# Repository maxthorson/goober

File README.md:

# Goober

Goober is a compact USB-C macro pad project with two connected halves:

- `website/` contains the public Next.js site for presenting the product, linking
  firmware resources, and experimenting with a hosted QMK configurator surface.
- `hardware/` contains the Rev A hardware package: KiCad PCB files, case models,
  QMK firmware, fabrication docs, mockups, validation notes, and release
  deliverables.

The hardware target is a 9-key RP2040-Zero macro pad with MX hot-swap switches,
an OLED display, a volume/mute knob, and individually addressable RGB lighting.
USB hub and charging passthrough are deferred.

## Project Status

Rev A.1 is a checked engineering prototype ready for a first fabrication and fit
test. It has not yet been built or electrically tested on physical hardware.

The hardware package passes schematic ERC, PCB DRC, and KiCad schematic/PCB
parity checks with zero issues. Firmware compiles, and the printable case
components validate as watertight single-body meshes.

## Repository Layout

| Folder | Purpose |
|---|---|
| `website/` | Next.js product site and QMK configurator integration |
| `hardware/case/` | OpenSCAD source and printable STL case files |
| `hardware/docs/` | Design, fabrication, assembly, firmware, and validation guides |
| `hardware/firmware/` | QMK board files, keymap, build script, and UF2 output |
| `hardware/hardware/` | KiCad schematic, PCB, Gerbers, BOM, and part references |
| `hardware/mockups/` | CAD renders, board images, and appearance concepts |
| `hardware/releases/` | Packaged Rev A prototype release archive |
| `hardware/tools/` | Project-owned helper scripts; large external tools are excluded |

## Start Here

For the site:

```bash
cd website
npm install
npm run dev
```

For the hardware:

1. Read `hardware/docs/DESIGN_PLAN.md` and
   `hardware/docs/PARTS_AND_COST.md`.
2. Use `hardware/docs/FABRICATION.md` to order a small PCB batch.
3. Print the fit coupon, then follow `hardware/docs/ASSEMBLY_AND_TEST.md`.
4. Flash the supplied UF2 or rebuild from `hardware/firmware/`.

## Notes

Large installed tools, virtual environments, downloaded toolchains, and upstream
source checkouts are intentionally not committed. License and provenance notes
for the hardware package are in `hardware/NOTICE.md`.

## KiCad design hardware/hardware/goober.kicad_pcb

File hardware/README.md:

# goober

A compact 9-key USB-C macro pad with MX hot-swap switches, an OLED, a volume/mute knob and individually addressable RGB lighting. RP2040-Zero + QMK. **USB hub and charging passthrough are deferred.**

**Rev A.1 is a checked engineering prototype, ready for a first fabrication and fit test. It has not yet been built or electrically tested on hardware.**

## Start here

1. Read [the design plan](docs/DESIGN_PLAN.md) and [parts/cost list](docs/PARTS_AND_COST.md).
2. Use [the fabrication guide](docs/FABRICATION.md) to order a small PCB batch.
3. Print the fit coupon, then follow [assembly and testing](docs/ASSEMBLY_AND_TEST.md).
4. Flash the supplied UF2. [Software and firmware instructions](docs/SOFTWARE_AND_FIRMWARE.md) explain editing and rebuilding.

KiCad, OpenSCAD and the firmware build tools are already installed on this Mac. You only need an optional printer slicer if printing at home. Your remaining work is choosing switches/keycaps, buying parts, printing or ordering the enclosure, soldering and testing the physical prototype.

## Files

| Deliverable | Location |
|---|---|
| Bare-board manufacturing ZIP | [Goober-Rev-A-Gerbers.zip](hardware/Goober-Rev-A-Gerbers.zip) |
| Editable PCB/schematic | [KiCad project](hardware/goober.kicad_pro) — keep adjacent files/libraries together |
| Printable case | [Base](case/goober-base.stl), [lid](case/goober-lid.stl), [knob](case/goober-knob.stl), [fit coupon](case/goober-fit-coupon.stl) |
| Editable case | [OpenSCAD source](case/goober.scad) |
| Ready-to-flash firmware | [Goober UF2](firmware/build/goober-rev-a-default.uf2) |
| Firmware source | [Default keymap](firmware/goober/rev_a/keymaps/default/keymap.c), plus board files in `firmware/goober/rev_a/` |
| Mockups | [Actual CAD](mockups/goober-cad.png), [exploded CAD](mockups/goober-exploded.png), [appearance concept](mockups/goober-appearance.png) |
| Parts list | [Guide](docs/PARTS_AND_COST.md), [CSV](hardware/BOM.csv) |
| Checks and remaining tests | [Validation record](docs/VALIDATION.md) |

The design passes schematic ERC, PCB DRC and KiCad schematic/PCB parity with zero issues. Firmware compiles; the base, lid and knob are watertight single-body meshes. The release includes the detailed validation results and checksums.

The archive in `releases/` contains the deliverables and editable project, without the large installed tools and upstream source checkouts. License/provenance notes are in [NOTICE.md](NOTICE.md).

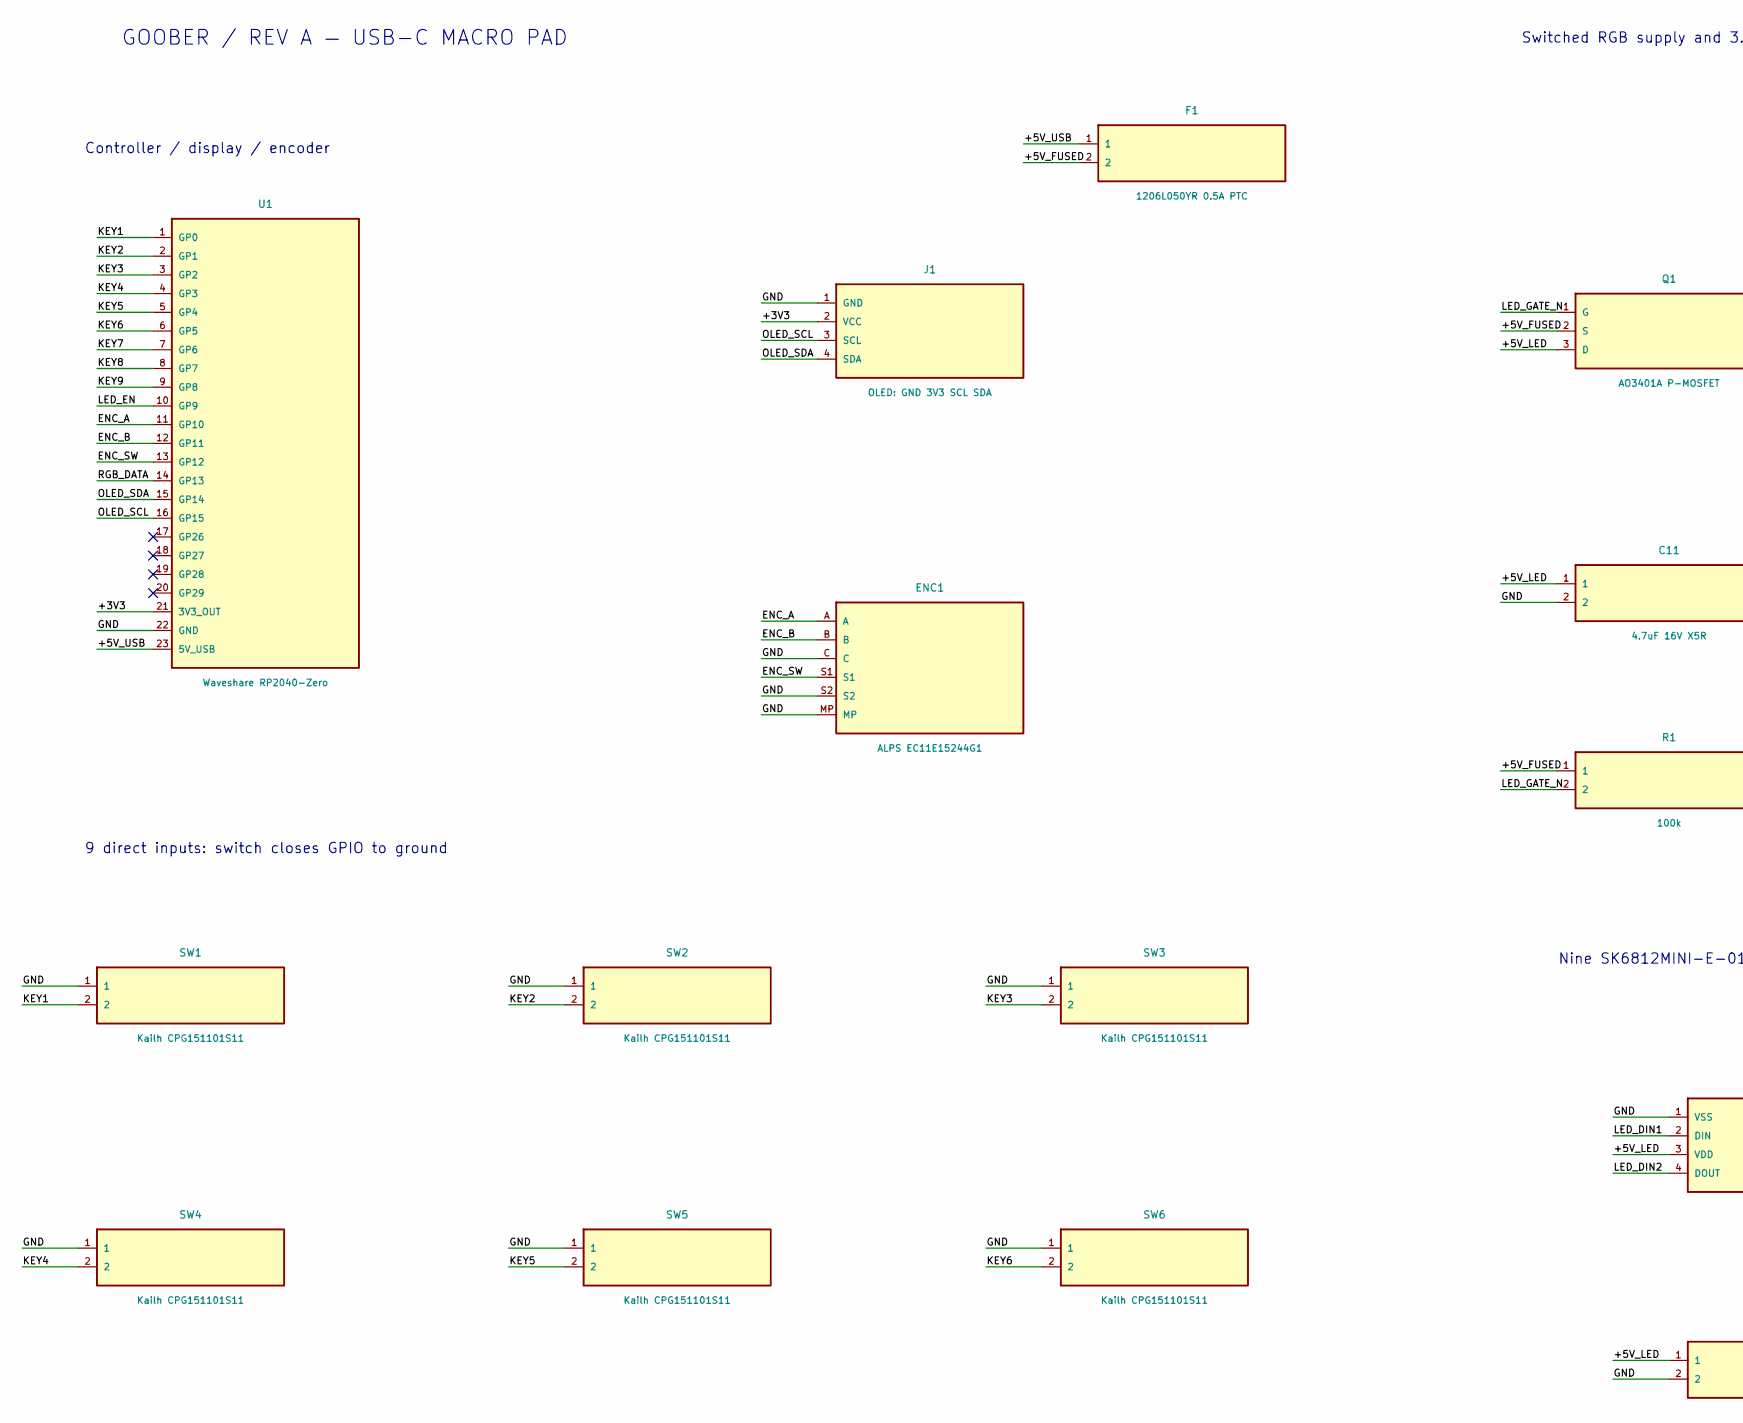
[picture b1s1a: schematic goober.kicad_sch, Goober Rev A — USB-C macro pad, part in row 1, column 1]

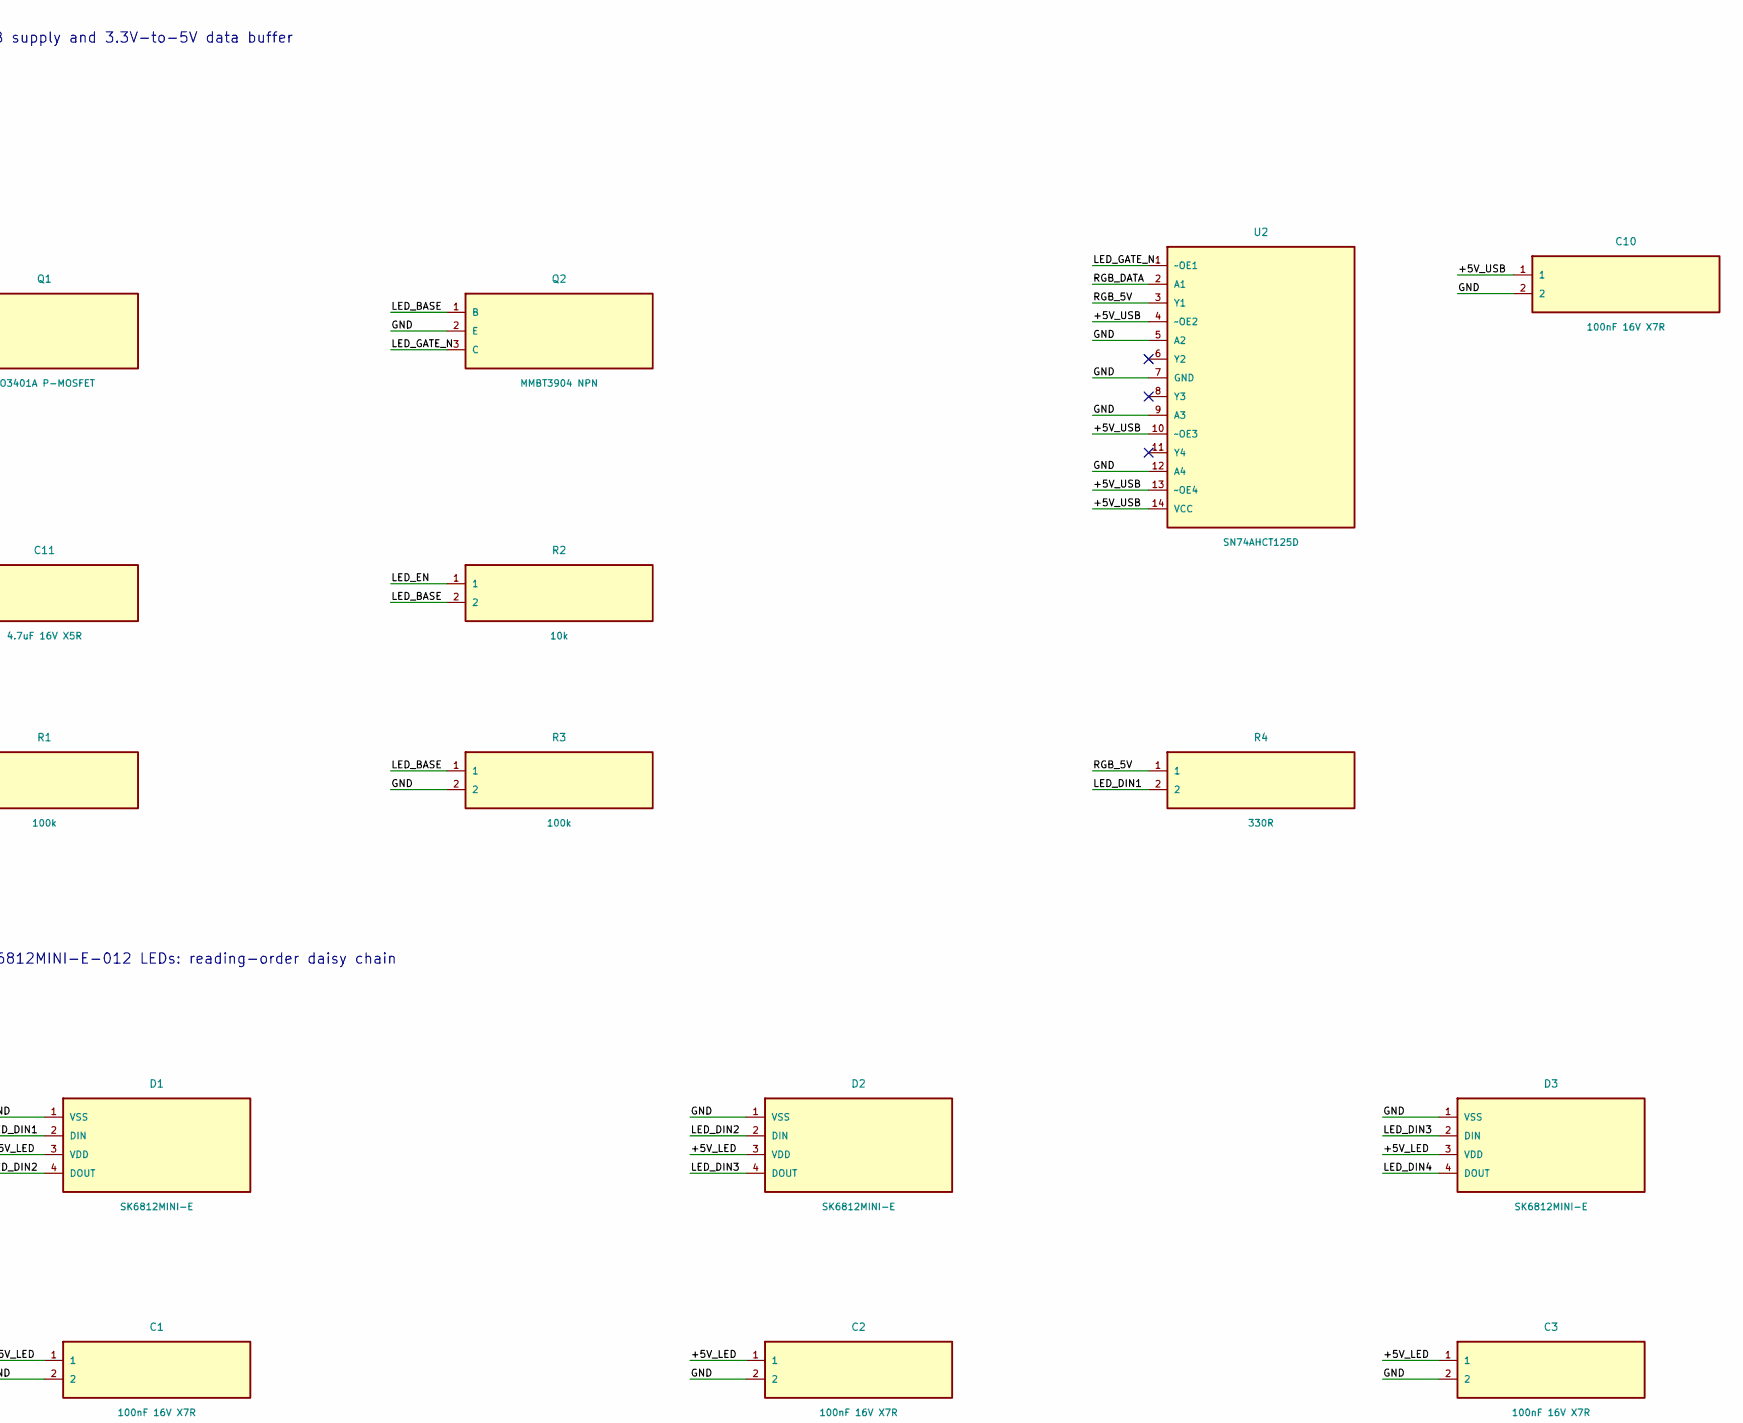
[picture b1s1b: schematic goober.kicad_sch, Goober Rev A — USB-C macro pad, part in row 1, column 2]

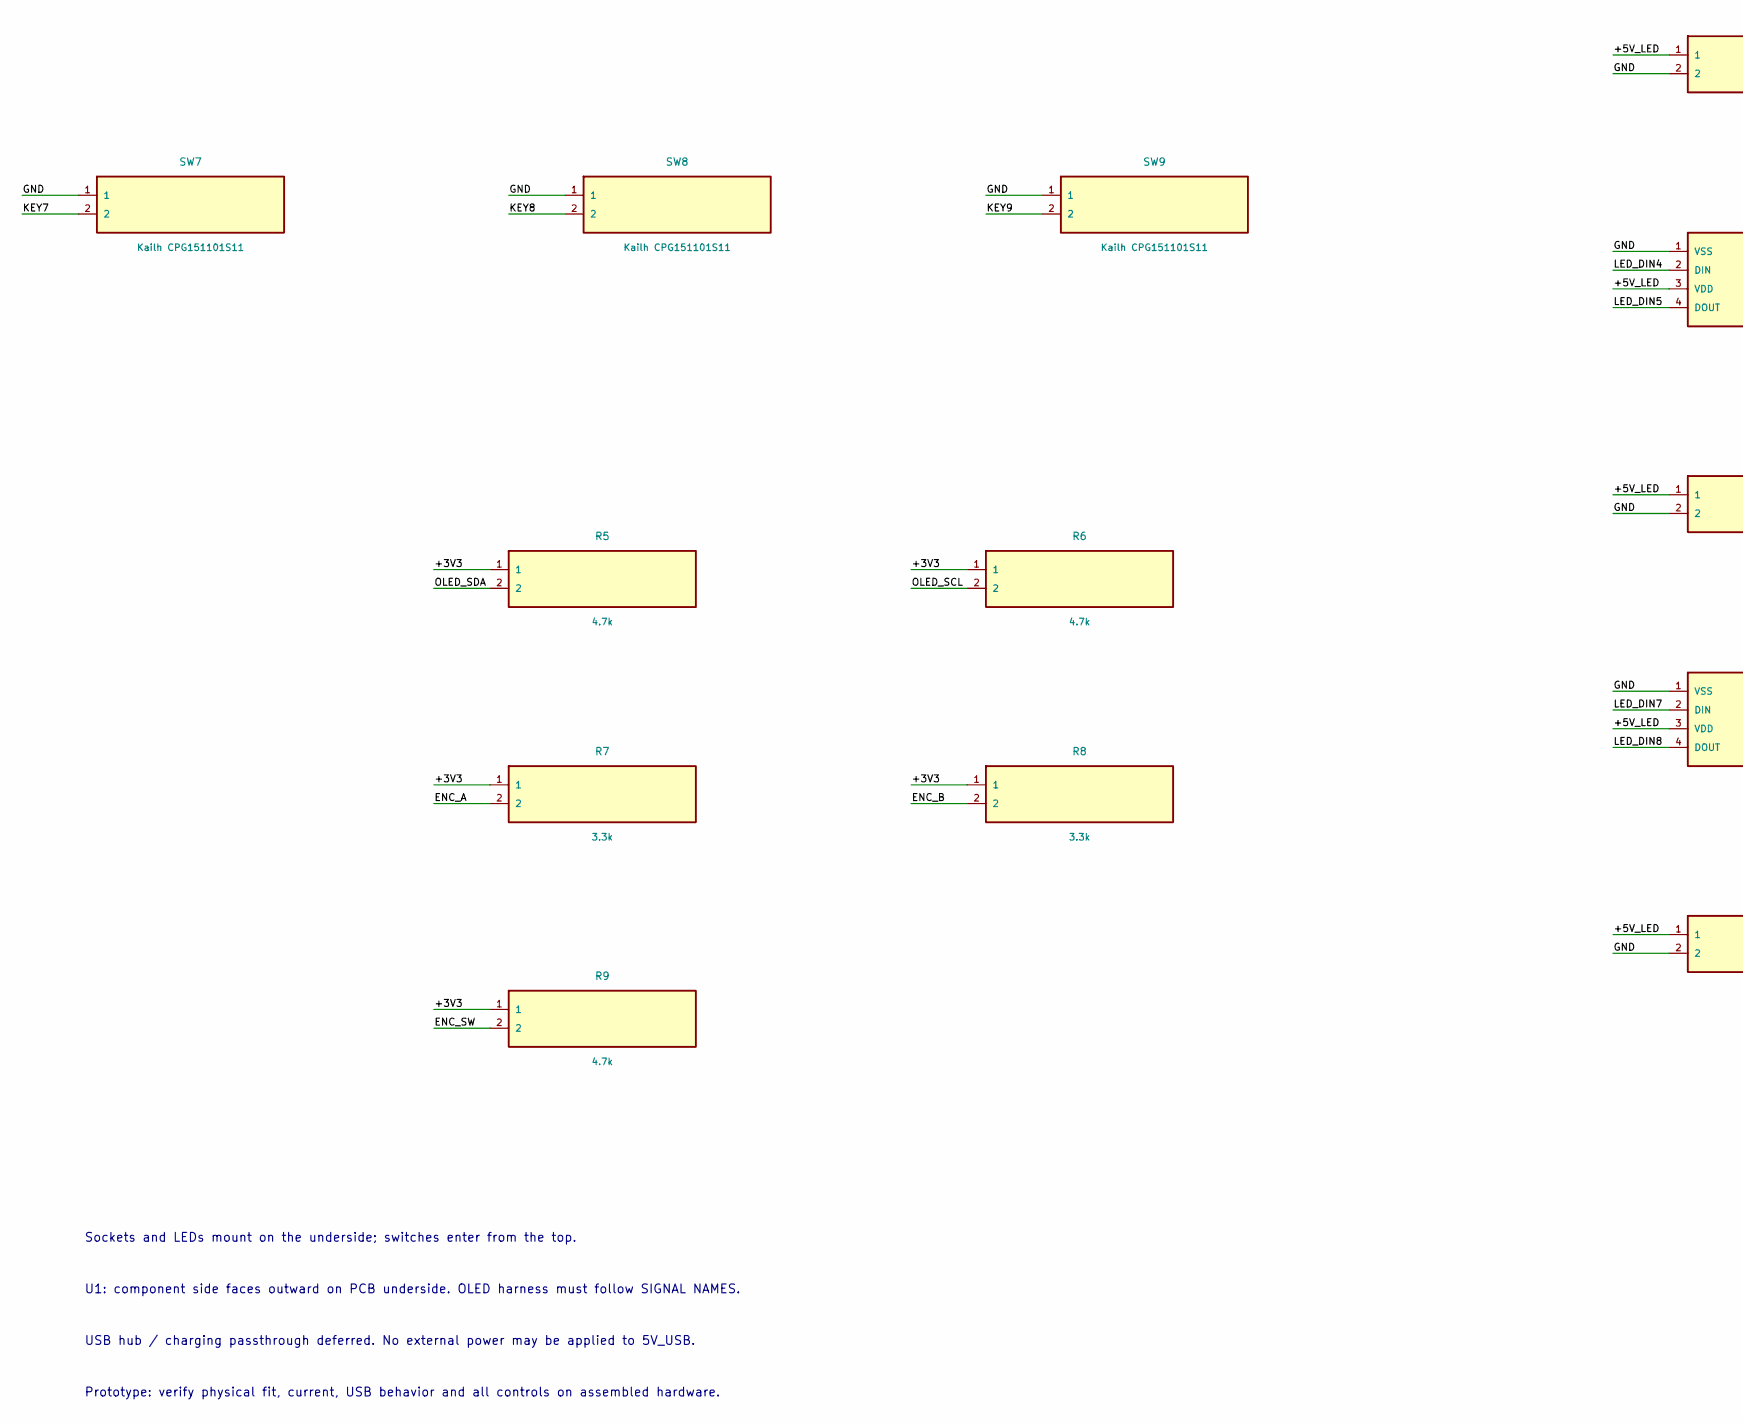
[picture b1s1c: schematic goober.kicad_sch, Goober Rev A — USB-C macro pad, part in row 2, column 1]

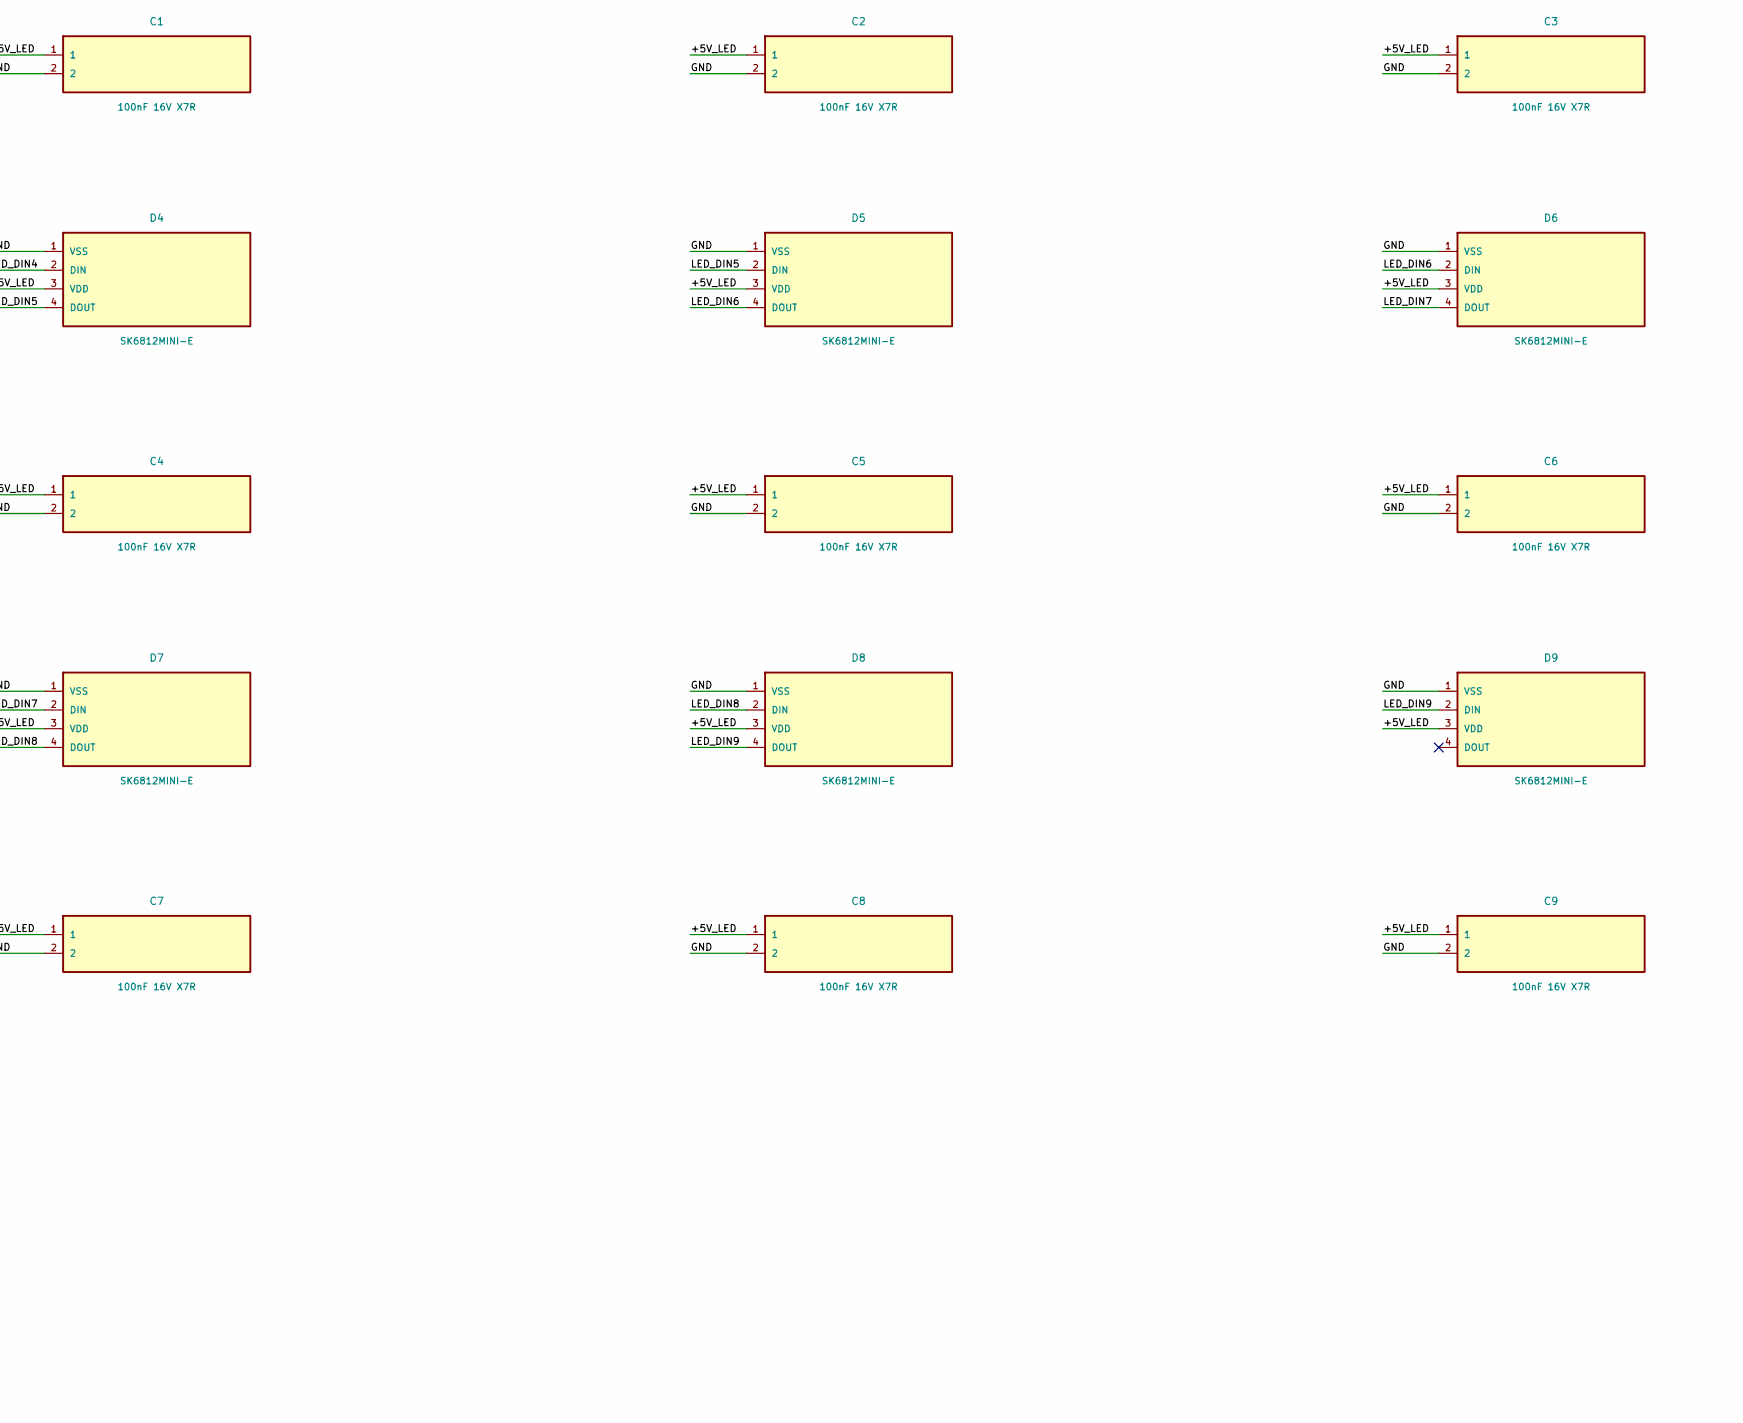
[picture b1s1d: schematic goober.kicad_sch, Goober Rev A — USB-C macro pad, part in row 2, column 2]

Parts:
C1, C2, C3, C4, C5, C6, C7, C8, C9, C10: 100nF 16V X7R; C_0805_2012Metric
C11: 4.7uF 16V X5R; C_0805_2012Metric
D1, D2, D3, D4, D5, D6, D7, D8, D9: SK6812MINI-E; LED_SK6812MINI-E_3.2x2.8mm_P1.5mm_ReverseMount
ENC1: ALPS EC11E15244G1; RotaryEncoder_Alps_EC11E-Switch_Vertical_H20mm
F1: 1206L050YR 0.5A PTC; Fuse_1206_3216Metric
J1: OLED: GND 3V3 SCL SDA; PinHeader_1x04_P2.54mm_Vertical
Q1: AO3401A P-MOSFET; SOT-23
Q2: MMBT3904 NPN; SOT-23
R1, R3: 100k; R_0805_2012Metric
R2: 10k; R_0805_2012Metric
R4: 330R; R_0805_2012Metric
R5, R6, R9: 4.7k; R_0805_2012Metric
R7, R8: 3.3k; R_0805_2012Metric
SW1, SW2, SW3, SW4, SW5, SW6, SW7, SW8, SW9: Kailh CPG151101S11; SW_MX_HS_CPG151101S11_1u
U1: Waveshare RP2040-Zero; RP2040_Zero_Headers
U2: SN74AHCT125D; SOIC-14_3.9x8.7mm_P1.27mm

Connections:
/+3V3: J1.2 (VCC), R5.1, R6.1, R7.1, R8.1, R9.1, U1.21 (3V3_OUT)
/+5V_FUSED: F1.2, Q1.2 (S), R1.1
/+5V_LED: C1.1, C2.1, C3.1, C4.1, C5.1, C6.1, C7.1, C8.1, C9.1, C11.1, D1.3 (VDD), D2.3 (VDD), D3.3 (VDD), D4.3 (VDD), D5.3 (VDD), D6.3 (VDD), D7.3 (VDD), D8.3 (VDD), D9.3 (VDD), Q1.3 (D)
/+5V_USB: C10.1, F1.1, U1.23 (5V_USB), U2.4 (~OE2), U2.10 (~OE3), U2.13 (~OE4), U2.14 (VCC)
/ENC_A: ENC1.A, R7.2, U1.11 (GP10)
/ENC_B: ENC1.B, R8.2, U1.12 (GP11)
/ENC_SW: ENC1.S1, R9.2, U1.13 (GP12)
/GND: C1.2, C2.2, C3.2, C4.2, C5.2, C6.2, C7.2, C8.2, C9.2, C10.2, C11.2, D1.1 (VSS), D2.1 (VSS), D3.1 (VSS), D4.1 (VSS), D5.1 (VSS), D6.1 (VSS), D7.1 (VSS), D8.1 (VSS), D9.1 (VSS), ENC1.C, ENC1.MP, ENC1.S2, J1.1 (GND), Q2.2 (E), R3.2, SW1.1, SW2.1, SW3.1, SW4.1, SW5.1, SW6.1, SW7.1, SW8.1, SW9.1, U1.22 (GND), U2.5 (A2), U2.7 (GND), U2.9 (A3), U2.12 (A4)
/KEY1: SW1.2, U1.1 (GP0)
/KEY2: SW2.2, U1.2 (GP1)
/KEY3: SW3.2, U1.3 (GP2)
/KEY4: SW4.2, U1.4 (GP3)
/KEY5: SW5.2, U1.5 (GP4)
/KEY6: SW6.2, U1.6 (GP5)
/KEY7: SW7.2, U1.7 (GP6)
/KEY8: SW8.2, U1.8 (GP7)
/KEY9: SW9.2, U1.9 (GP8)
/LED_BASE: Q2.1 (B), R2.2, R3.1
/LED_DIN1: D1.2 (DIN), R4.2
/LED_DIN2: D1.4 (DOUT), D2.2 (DIN)
/LED_DIN3: D2.4 (DOUT), D3.2 (DIN)
/LED_DIN4: D3.4 (DOUT), D4.2 (DIN)
/LED_DIN5: D4.4 (DOUT), D5.2 (DIN)
/LED_DIN6: D5.4 (DOUT), D6.2 (DIN)
/LED_DIN7: D6.4 (DOUT), D7.2 (DIN)
/LED_DIN8: D7.4 (DOUT), D8.2 (DIN)
/LED_DIN9: D8.4 (DOUT), D9.2 (DIN)
/LED_EN: R2.1, U1.10 (GP9)
/LED_GATE_N: Q1.1 (G), Q2.3 (C), R1.2, U2.1 (~OE1)
/OLED_SCL: J1.3 (SCL), R6.2, U1.16 (GP15)
/OLED_SDA: J1.4 (SDA), R5.2, U1.15 (GP14)
/RGB_5V: R4.1, U2.3 (Y1)
/RGB_DATA: U1.14 (GP13), U2.2 (A1)

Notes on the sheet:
GOOBER / REV A — USB-C MACRO PAD
Controller / display / encoder
9 direct inputs: switch closes GPIO to ground
Switched RGB supply and 3.3V-to-5V data buffer
Nine SK6812MINI-E-012 LEDs: reading-order daisy chain
Sockets and LEDs mount on the underside; switches enter from the top.
U1: component side faces outward on PCB underside. OLED harness must follow SIGNAL NAMES.
USB hub / charging passthrough deferred. No external power may be applied to 5V_USB.
Prototype: verify physical fit, current, USB behavior and all controls on assembled hardware.

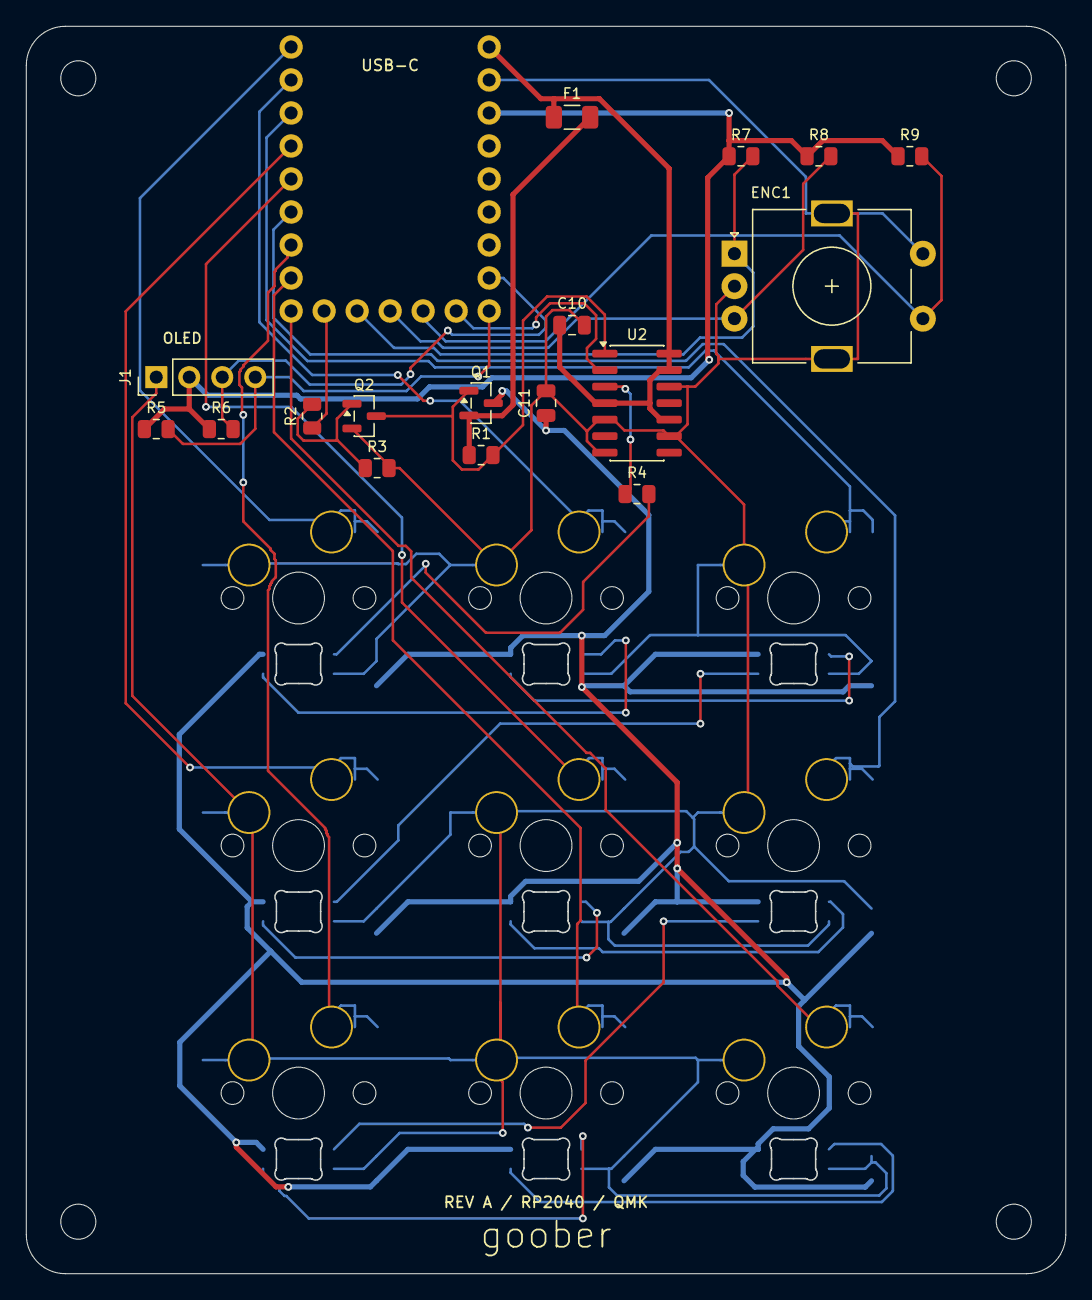
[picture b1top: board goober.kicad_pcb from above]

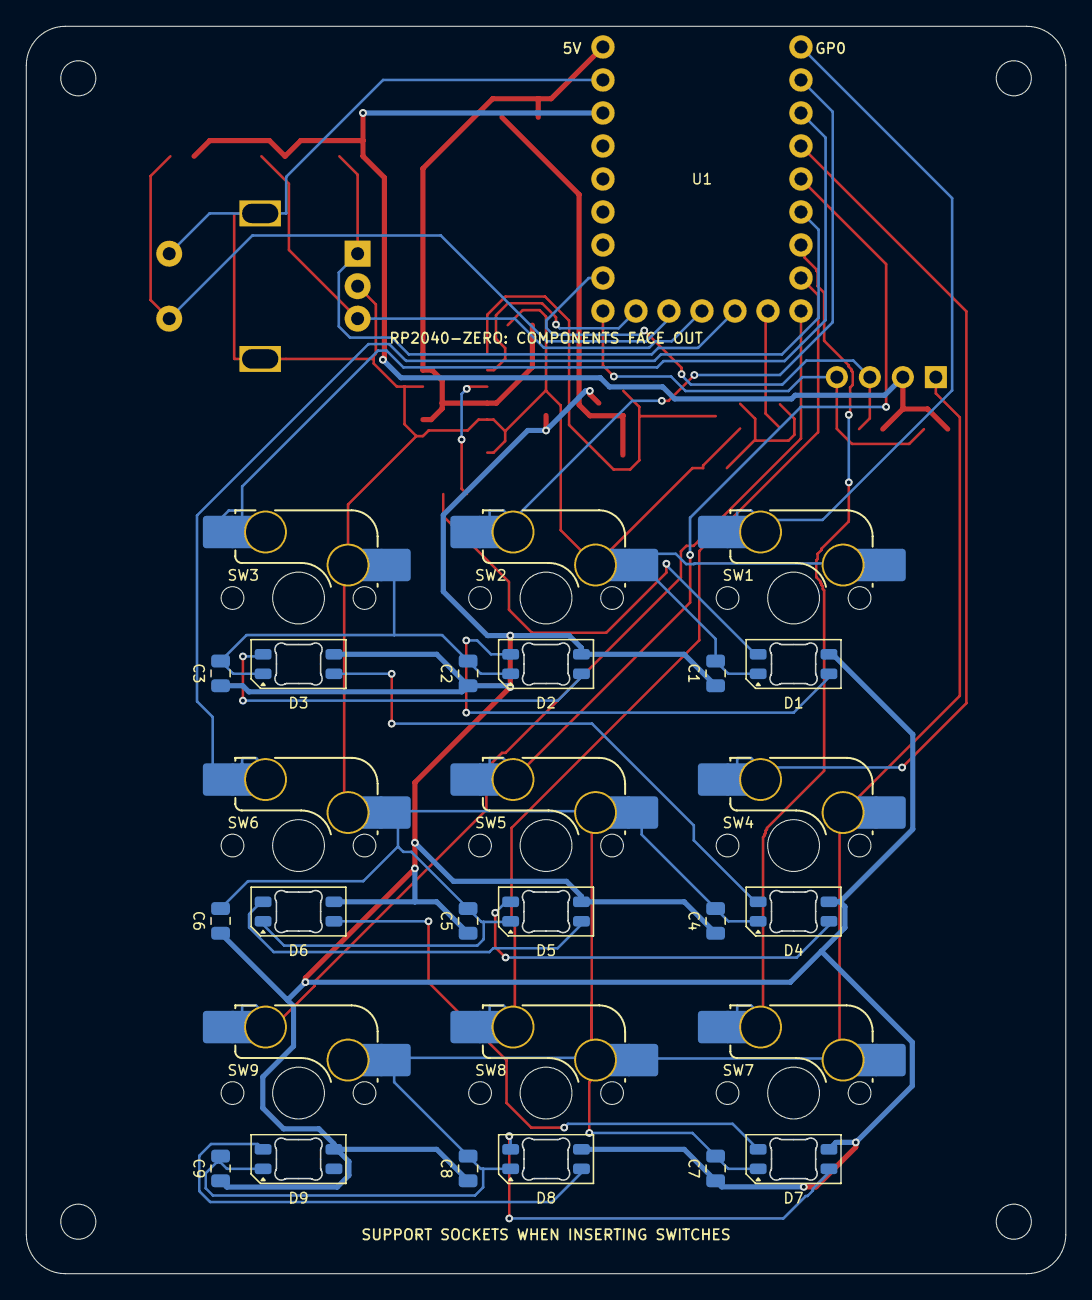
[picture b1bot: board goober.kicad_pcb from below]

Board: 2 copper layers, 79.9 x 95.9 mm, 49 parts (28 on the bottom side), 33 nets.

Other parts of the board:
H1, H2, H3, H4: M2.5 mounting; MountingHole_2.7mm_M2.5

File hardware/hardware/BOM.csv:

Reference,Quantity,Description,Manufacturer part or selection,Footprint,Side,Notes
U1,1,Waveshare RP2040-Zero,Waveshare RP2040-Zero,RP2040_Zero_Headers,B,Bottom; components outward/down; 3.0 mm board-to-module-back gap; needs 23 header pins
SW1,1,Kailh CPG151101S11,CPG151101S11,SW_MX_HS_CPG151101S11_1u,B,Socket only; purchase actual MX switches separately
D1,1,SK6812MINI-E,SK6812MINI-E-012,LED_SK6812MINI-E_3.2x2.8mm_P1.5mm_ReverseMount,B,"Reverse mount through window; pin1 GND,2 DIN,3 VDD,4 DOUT"
C1,1,100nF 16V X7R,,C_0805_2012Metric,B,
SW2,1,Kailh CPG151101S11,CPG151101S11,SW_MX_HS_CPG151101S11_1u,B,Socket only; purchase actual MX switches separately
D2,1,SK6812MINI-E,SK6812MINI-E-012,LED_SK6812MINI-E_3.2x2.8mm_P1.5mm_ReverseMount,B,"Reverse mount through window; pin1 GND,2 DIN,3 VDD,4 DOUT"
C2,1,100nF 16V X7R,,C_0805_2012Metric,B,
SW3,1,Kailh CPG151101S11,CPG151101S11,SW_MX_HS_CPG151101S11_1u,B,Socket only; purchase actual MX switches separately
D3,1,SK6812MINI-E,SK6812MINI-E-012,LED_SK6812MINI-E_3.2x2.8mm_P1.5mm_ReverseMount,B,"Reverse mount through window; pin1 GND,2 DIN,3 VDD,4 DOUT"
C3,1,100nF 16V X7R,,C_0805_2012Metric,B,
SW4,1,Kailh CPG151101S11,CPG151101S11,SW_MX_HS_CPG151101S11_1u,B,Socket only; purchase actual MX switches separately
D4,1,SK6812MINI-E,SK6812MINI-E-012,LED_SK6812MINI-E_3.2x2.8mm_P1.5mm_ReverseMount,B,"Reverse mount through window; pin1 GND,2 DIN,3 VDD,4 DOUT"
C4,1,100nF 16V X7R,,C_0805_2012Metric,B,
SW5,1,Kailh CPG151101S11,CPG151101S11,SW_MX_HS_CPG151101S11_1u,B,Socket only; purchase actual MX switches separately
D5,1,SK6812MINI-E,SK6812MINI-E-012,LED_SK6812MINI-E_3.2x2.8mm_P1.5mm_ReverseMount,B,"Reverse mount through window; pin1 GND,2 DIN,3 VDD,4 DOUT"
C5,1,100nF 16V X7R,,C_0805_2012Metric,B,
SW6,1,Kailh CPG151101S11,CPG151101S11,SW_MX_HS_CPG151101S11_1u,B,Socket only; purchase actual MX switches separately
D6,1,SK6812MINI-E,SK6812MINI-E-012,LED_SK6812MINI-E_3.2x2.8mm_P1.5mm_ReverseMount,B,"Reverse mount through window; pin1 GND,2 DIN,3 VDD,4 DOUT"
C6,1,100nF 16V X7R,,C_0805_2012Metric,B,
SW7,1,Kailh CPG151101S11,CPG151101S11,SW_MX_HS_CPG151101S11_1u,B,Socket only; purchase actual MX switches separately
D7,1,SK6812MINI-E,SK6812MINI-E-012,LED_SK6812MINI-E_3.2x2.8mm_P1.5mm_ReverseMount,B,"Reverse mount through window; pin1 GND,2 DIN,3 VDD,4 DOUT"
C7,1,100nF 16V X7R,,C_0805_2012Metric,B,
SW8,1,Kailh CPG151101S11,CPG151101S11,SW_MX_HS_CPG151101S11_1u,B,Socket only; purchase actual MX switches separately
D8,1,SK6812MINI-E,SK6812MINI-E-012,LED_SK6812MINI-E_3.2x2.8mm_P1.5mm_ReverseMount,B,"Reverse mount through window; pin1 GND,2 DIN,3 VDD,4 DOUT"
C8,1,100nF 16V X7R,,C_0805_2012Metric,B,
SW9,1,Kailh CPG151101S11,CPG151101S11,SW_MX_HS_CPG151101S11_1u,B,Socket only; purchase actual MX switches separately
D9,1,SK6812MINI-E,SK6812MINI-E-012,LED_SK6812MINI-E_3.2x2.8mm_P1.5mm_ReverseMount,B,"Reverse mount through window; pin1 GND,2 DIN,3 VDD,4 DOUT"
C9,1,100nF 16V X7R,,C_0805_2012Metric,B,
ENC1,1,ALPS EC11E15244G1,EC11E15244G1,RotaryEncoder_Alps_EC11E-Switch_Vertical_H20mm,F,
J1,1,OLED: GND 3V3 SCL SDA,Direct soldered 4-wire harness,PinHeader_1x04_P2.54mm_Vertical,F,No tall header; wire OLED by signal names GND/VCC/SCL/SDA
U2,1,SN74AHCT125D,SN74AHCT125DR,SOIC-14_3.9x8.7mm_P1.27mm,F,
Q1,1,AO3401A P-MOSFET,AO3401A,SOT-23,F,
Q2,1,MMBT3904 NPN,MMBT3904LT1G,SOT-23,F,
R1,1,100k,,R_0805_2012Metric,F,
R2,1,10k,,R_0805_2012Metric,F,
R3,1,100k,,R_0805_2012Metric,F,
R4,1,330R,,R_0805_2012Metric,F,
R5,1,4.7k,,R_0805_2012Metric,F,
R6,1,4.7k,,R_0805_2012Metric,F,
R7,1,3.3k,,R_0805_2012Metric,F,
R8,1,3.3k,,R_0805_2012Metric,F,
R9,1,4.7k,,R_0805_2012Metric,F,
C10,1,100nF 16V X7R,,C_0805_2012Metric,F,
C11,1,4.7uF 16V X5R,,C_0805_2012Metric,F,
F1,1,1206L050YR 0.5A PTC,1206L050YR,Fuse_1206_3216Metric,F,
OLED,1,128x32 monochrome OLED,Waveshare 0.91inch OLED Module SKU14657,,Off-board,36x12.5mm; 3.3V I2C
SWITCHES,9,Standard-height RGB-compatible MX switches,User choice,,Off-board,3-pin or5-pin; 1.5mm plate
KEYCAPS,9,1u MX-stem keycaps,User choice,,Off-board,Uniform profile suggested
U1_PINS,23,2.54mm pitch 0.64mm square header pins,Breakaway 2x9 +1x5,,Off-board,3.0mm gap between boards
INSERTS,4,M2.5 brass heat-set inserts,OD3.8 x L4.0mm,,Off-board,Test coupon first
SCREWS_FRONT,2,M2.5 x12mm machine screw,Pan/button head,,Off-board,Front key side
SCREWS_REAR,2,M2.5 x18mm machine screw,Pan/button head,,Off-board,Rear hood side
FEET,4,8mm adhesive rubber feet,User choice,,Off-board,Thickness >=1mm
CASE_BASE,1,Printed base,goober-base.stl,,Off-board,Millimetres; 100%
CASE_LID,1,Printed lid,goober-lid.stl,,Off-board,Print with appropriate supports
KNOB,1,Printed 6mm D-shaft knob,goober-knob.stl,,Off-board,Fit test actual shaft
USB_CABLE,1,USB-C data cable,Match Mac port,,Off-board,Plug overmold fits14x8mm opening
OLED_TAPE,1,Thin double-sided electronics tape,Small amount,,Off-board,"PCB ledges only, not glass"

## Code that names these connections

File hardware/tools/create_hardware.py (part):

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    return f

rp_pins={str(i+1):'KEY'+str(i+1) for i in range(9)}
rp_pins.update({'10':'LED_EN','11':'ENC_A','12':'ENC_B','13':'ENC_SW','14':'RGB_DATA',
               '15':'OLED_SDA','16':'OLED_SCL','17':None,'18':None,'19':None,'20':None,
               '21':'+3V3','22':'GND','23':'+5V_USB'})
rp_names={str(i+1):'GP'+str(i) for i in range(16)}
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    {'A':'ENC_A','B':'ENC_B','C':'GND','S1':'ENC_SW','S2':'GND','MP':'GND'})
# OLED is wired by signal name; this 2.54-mm header is not a claimed pin-for-pin PH connector.
add('J1','OLED: GND 3V3 SCL SDA','Connector_PinHeader_2.54mm','PinHeader_1x04_P2.54mm_Vertical',10,27,
    {'1':'GND','2':'+3V3','3':'OLED_SCL','4':'OLED_SDA'},angle=90,
    pin_names={'1':'GND','2':'VCC','3':'SCL','4':'SDA'})
add('U2','SN74AHCT125D','Package_SO','SOIC-14_3.9x8.7mm_P1.27mm',47,29,
    {'1':'LED_GATE_N','2':'RGB_DATA','3':'RGB_5V','4':'+5V_USB','5':'GND','6':None,'7':'GND',
     '8':None,'9':'GND','10':'+5V_USB','11':None,'12':'GND','13':'+5V_USB','14':'+5V_USB'},
    pin_names={'1':'~OE1','2':'A1','3':'Y1','4':'~OE2','5':'A2','6':'Y2','7':'GND','8':'Y3','9':'A3','10':'~OE3','11':'Y4','12':'A4','13':'~OE4','14':'VCC'},
    pin_types={'1':'input','2':'input','3':'tri_state','4':'input','5':'input','6':'tri_state','7':'power_in','8':'tri_state','9':'input','10':'input','11':'tri_state','12':'input','13':'input','14':'power_in'})
add('Q1','AO3401A P-MOSFET','Package_TO_SOT_SMD','SOT-23',35,29,{'1':'LED_GATE_N','2':'+5V_FUSED','3':'+5V_LED'},pin_names={'1':'G','2':'S','3':'D'})
add('Q2','MMBT3904 NPN','Package_TO_SOT_SMD','SOT-23',26,30,{'1':'LED_BASE','2':'GND','3':'LED_GATE_N'},pin_names={'1':'B','2':'E','3':'C'})
def res(ref,val,x,y,pins,angle=0):return add(ref,val,'Resistor_SMD','R_0805_2012Metric',x,y,pins,angle=angle)
res('R1','100k',35,33,{'1':'+5V_FUSED','2':'LED_GATE_N'})
res('R2','10k',22,30,{'1':'LED_EN','2':'LED_BASE'},90)
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
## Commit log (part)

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2025-09-30 Initial commit from Create Next App
2025-10-01 made a base website that will serve as the cover
2025-10-01 cleanup
2025-10-01 customized front page, added products placeholder, added qmk config.
    future plans
    - add products
    - add blog
    - make things look nice
2025-10-03 they hit the second princess tower (boss bandit)
2025-10-03 it was bush
